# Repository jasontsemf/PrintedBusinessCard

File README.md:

# Printed Business Card (PBC)

```
A business card not printed on paper, but FR-4.
```

[Project site](https://jasontsemf.github.io/pbc.html)

## The Process

```
Coming soon...
```

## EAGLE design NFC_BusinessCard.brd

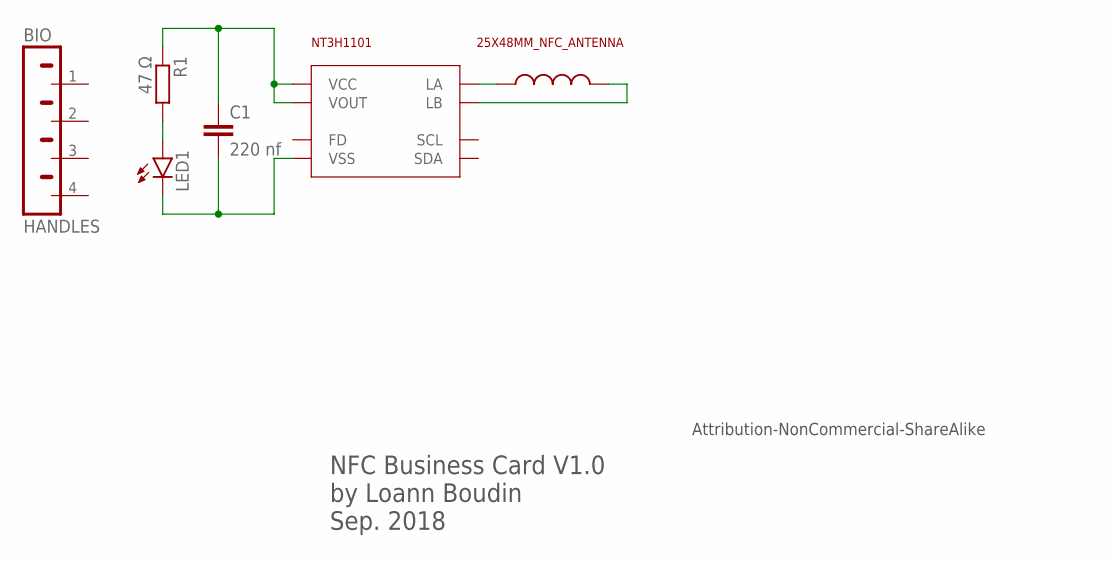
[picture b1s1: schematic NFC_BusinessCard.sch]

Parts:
ANT: 25X48MM_NFC_ANTENNA; 25X48MM_NFC
BIO: HANDLES; MA08-1
C1: 220 nf; C0603
LED1: LEDSML0805; SML0805
NT3H1101: NT3H; XQFN8
R1: 47 Ω; R0603

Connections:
unnamed: ANT.P$2, NT3H1101.LA
unnamed: ANT.P$1, NT3H1101.LB
unnamed: C1.1, NT3H1101.VCC, NT3H1101.VOUT, R1.1
unnamed: LED1.A, R1.2
unnamed: C1.2, LED1.C, NT3H1101.VSS

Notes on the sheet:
NFC Business Card V1.0 by Loann Boudin Sep. 2018
Attribution-NonCommercial-ShareAlike

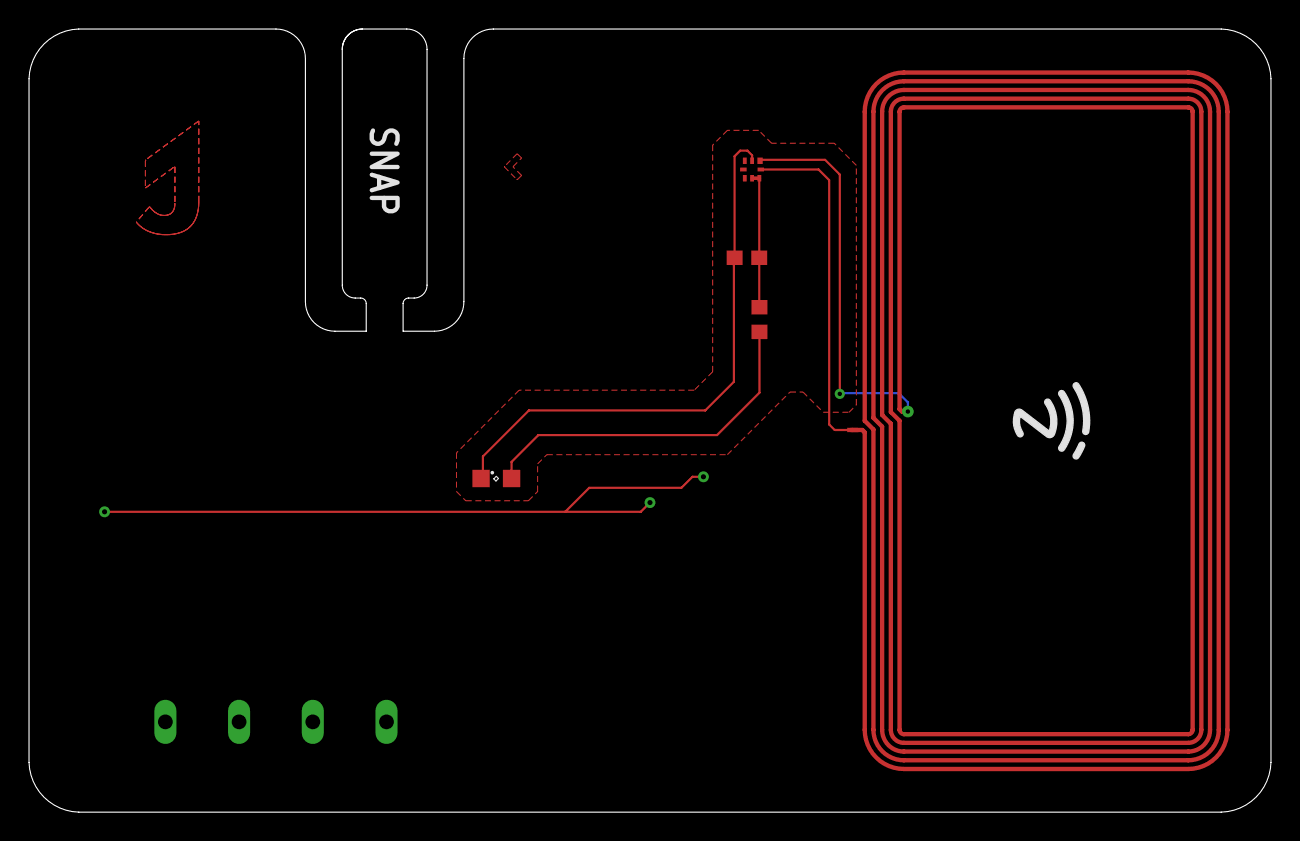
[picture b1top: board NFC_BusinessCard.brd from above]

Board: 2 copper layers, 85.6 x 54.0 mm, 6 parts (1 on the bottom side), 5 nets.

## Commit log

2020-07-31 added readme
